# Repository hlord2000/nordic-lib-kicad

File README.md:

# Nordic Semiconductor KiCad Library

---
# A KiCad 10 library for all modern Nordic Semiconductor parts.

KLC compliance is established using KiCad's official scripts within the "kicad-library-utils" folder and the "lib_check.sh" script

Compliance for the purposes of this library is defined as zero errors for footprints and symbols. Reasonable warnings about pin position or names may be accepted.

## Installation instructions

Open the KiCad Plugin and Content Manager (PCM), click "Manage..." in the top right, and add the following URL to your list of repositories:
```
https://raw.githubusercontent.com/hlord2000/hlord2000-kicad-repository/main/repository.json
```
Then, using the dropdown in the PCM, switch to "hlord2000's KiCad Repository" and click on the "Libraries" tab.

## Seeking pull-requests for any footprint/symbol/reference design block/3D model marked 🚧

 # nRF9 series - Cellular

|             | Symbol | Footprint | Reference Design Block | 3D Model | KLC Compliant |
|-------------|--------|-----------|------------------------|----------|---------------|
| [nRF9151](https://www.nordicsemi.com/products/nrf9151) LGA |✅|✅|🚧|✅|🚧|
| [nRF9161](https://www.nordicsemi.com/products/nrf9161) LGA |✅|✅|🚧|✅|🚧|
| [nRF9160](https://www.nordicsemi.com/products/nrf9160) LGA |✅|✅|🚧|✅|🚧|

 # nRF7 series - Wi-Fi

|             | Symbol | Footprint | Reference Design Block | 3D Model | KLC Compliant |
|-------------|--------|-----------|------------------------|----------|---------------|
| [nRF7002](https://www.nordicsemi.com/products/nrf7002) QFN |✅|✅|🚧|✅|🚧| 
| [nRF7002](https://www.nordicsemi.com/products/nrf7002) WLCSP |✅|✅|🚧|✅|🚧| 
| [nRF7001](https://www.nordicsemi.com/products/nrf7001) QFN |✅|✅|🚧|✅|🚧| 
| [nRF7000](https://www.nordicsemi.com/products/nrf7000) QFN |✅|✅|🚧|✅|🚧| 

# nRF54L series - Bluetooth Low Energy

|             | Symbol | Footprint | Reference Design Block | 3D Model | KLC Compliant |
|-------------|--------|-----------|------------------------|----------|---------------|
| [nRF54LM20A](https://www.nordicsemi.com/Products/nRF54LM20A) QFN-52 |✅|✅|✅|✅|🚧| 
| [nRF54LM20A](https://www.nordicsemi.com/Products/nRF54LM20A) FCCSP |✅|✅|✅|✅|🚧| 
| [nRF54L15](https://www.nordicsemi.com/products/nrf54l15) QFN-52 |✅|✅|✅|✅|🚧| 
| [nRF54L15](https://www.nordicsemi.com/products/nrf54l15) QFN-48 |✅|✅|✅|✅|🚧| 
| [nRF54L15](https://www.nordicsemi.com/products/nrf54l15) QFN-40 |✅|✅|✅|✅|🚧| 
| [nRF54L15](https://www.nordicsemi.com/products/nrf54l15) WLCSP |✅|✅|✅|✅|🚧| 
| [nRF54L10](https://www.nordicsemi.com/products/nrf54l10) QFN-52 |✅|✅|✅|✅|🚧| 
| [nRF54L10](https://www.nordicsemi.com/products/nrf54l10) QFN-48 |✅|✅|✅|✅|🚧| 
| [nRF54L10](https://www.nordicsemi.com/products/nrf54l10) QFN-40 |✅|✅|✅|✅|🚧| 
| [nRF54LV10A](https://www.nordicsemi.com/products/nrf54lv10) CSP-29 |✅|✅|🚧|✅|🚧| 
| [nRF54LV10A](https://www.nordicsemi.com/products/nrf54lv10) QFN-48 |✅|✅|🚧|✅|🚧| 
| [nRF54LS05A](https://www.nordicsemi.com/Products/nRF54LS05A) QFN-48 |✅|✅|🚧|✅|🚧| 
| [nRF54LS05B](https://www.nordicsemi.com/Products/nRF54LS05B) QFN-48 |✅|✅|🚧|✅|🚧| 
| [nRF54L05](https://www.nordicsemi.com/products/nrf54l05) QFN-52 |✅|✅|✅|✅|🚧| 
| [nRF54L05](https://www.nordicsemi.com/products/nrf54l05) QFN-48 |✅|✅|✅|✅|🚧| 
| [nRF54L05](https://www.nordicsemi.com/products/nrf54l05) QFN-40 |✅|✅|✅|✅|🚧| 

 # nRF53 series - Bluetooth Low Energy

|             | Symbol | Footprint | Reference Design Block | 3D Model | KLC Compliant |
|-------------|--------|-----------|------------------------|----------|---------------|
| [nRF5340](https://www.nordicsemi.com/products/nrf5340) aQFN |✅|✅|🚧|🚧|🚧| 
| [nRF5340](https://www.nordicsemi.com/products/nrf5340) WLCSP |✅|✅|🚧|🚧|🚧| 

 # nRF52 series - Bluetooth Low Energy

|             | Symbol | Footprint | Reference Design Block | 3D Model | KLC Compliant |
|-------------|--------|-----------|------------------------|----------|---------------|
| [nRF52840](https://www.nordicsemi.com/products/nrf52840) aQFN |✅|✅|🚧|✅|🚧| 
| [nRF52840](https://www.nordicsemi.com/products/nrf52840) WLCSP |✅|✅|🚧|🚧|🚧| 
| [nRF52840](https://www.nordicsemi.com/products/nrf52840) QFN |✅|✅|🚧|✅|🚧| 
| [nRF52833](https://www.nordicsemi.com/products/nrf52833) aQFN |✅|✅|🚧|🚧|🚧| 
| [nRF52833](https://www.nordicsemi.com/products/nrf52833) WLCSP |✅|✅|🚧|🚧|🚧| 
| [nRF52833](https://www.nordicsemi.com/products/nrf52833) QFN |✅|✅|🚧|✅|🚧| 
| [nRF52832](https://www.nordicsemi.com/products/nrf52832) WLCSP |✅|✅|🚧|🚧|🚧| 
| [nRF52832](https://www.nordicsemi.com/products/nrf52832) QFN |✅|✅|🚧|✅|🚧| 
| [nRF52820](https://www.nordicsemi.com/products/nrf52820) WLCSP |✅|✅|🚧|🚧|🚧| 
| [nRF52820](https://www.nordicsemi.com/products/nrf52820) QFN |✅|✅|🚧|✅|🚧| 
| [nRF52811](https://www.nordicsemi.com/products/nrf52811) WLCSP |✅|✅|🚧|✅|🚧| 
| [nRF52811](https://www.nordicsemi.com/products/nrf52811) QFN-32 |✅|✅|🚧|✅|🚧| 
| [nRF52811](https://www.nordicsemi.com/products/nrf52811) QFN-48 |✅|✅|🚧|✅|🚧| 
| [nRF52810](https://www.nordicsemi.com/products/nrf52810) WLCSP |✅|✅|🚧|✅|🚧| 
| [nRF52810](https://www.nordicsemi.com/products/nrf52810) QFN-32 |✅|✅|🚧|✅|🚧| 
| [nRF52810](https://www.nordicsemi.com/products/nrf52810) QFN-48 |✅|✅|🚧|✅|🚧| 
| [nRF52805](https://www.nordicsemi.com/products/nrf52805) WLCSP |✅|✅|🚧|✅|🚧| 

 # nRF52 series - Modules

|             | Symbol | Footprint | Reference Design Block | 3D Model | KLC Compliant |
|-------------|--------|-----------|------------------------|----------|---------------|
| [E73-2G4M08S1C](https://www.ebyte.com/product-view-news.html?id=787) LGA module |✅|✅|🚧|✅|🚧|
| [ISP1907-LL](https://www.insightsip.com/products/bluetooth-low-energy/isp1907) LGA module |✅|✅|🚧|✅|🚧|

 # nRF21 series - PA + LNA ICs

|             | Symbol | Footprint | Reference Design Block | 3D Model | KLC Compliant |
|-------------|--------|-----------|------------------------|----------|---------------|
| [nRF21540](https://www.nordicsemi.com/products/nrf21540) QFN |✅|✅|🚧|✅|✅| 

 # nRF53 series - Modules

|             | Symbol | Footprint | Reference Design Block | 3D Model | KLC Compliant |
|-------------|--------|-----------|------------------------|----------|---------------|
| [E83-2G4M03S](https://www.ebyte.com/product-view-news.html?id=1307) LGA module |✅|✅|🚧|✅|🚧|
| [ISP2053-AX](https://www.insightsip.com/products/bluetooth-low-energy-and-802-15-4/isp2053) LGA module |✅|✅|🚧|✅|🚧|

 # nRF54 series - Modules

|             | Symbol | Footprint | Reference Design Block | 3D Model | KLC Compliant |
|-------------|--------|-----------|------------------------|----------|---------------|
| BC15C LGA module |✅|✅|🚧|✅|🚧|
| BC15M LGA module |✅|✅|🚧|✅|🚧|
| BL54L15-453-000xxx LGA module |✅|✅|🚧|✅|🚧|
| BL54L10-453-000xxx LGA module |✅|✅|🚧|✅|🚧|
| BM15x LGA module |✅|✅|🚧|✅|🚧|
| BM20x LGA module |✅|✅|🚧|✅|🚧|

 # nPM Power Management ICs

|             | Symbol | Footprint | Reference Design Block | 3D Model | KLC Compliant |
|-------------|--------|-----------|------------------------|----------|---------------|
| [nPM6001](https://www.nordicsemi.com/products/nPM6001) WLCSP |✅|✅|🚧|🚧|✅| 
| [nPM2100](https://www.nordicsemi.com/products/nPM2100) WLCSP |✅|✅|🚧|✅|✅| 
| [nPM2100](https://www.nordicsemi.com/products/nPM2100) QFN |✅|✅|🚧|✅|✅| 
| [nPM1300](https://www.nordicsemi.com/products/nPM1300) WLCSP |✅|✅|🚧|🚧|✅| 
| [nPM1300](https://www.nordicsemi.com/products/nPM1300) QFN |✅|✅|🚧|✅|✅| 
| [nPM1100](https://www.nordicsemi.com/products/nPM1100) WLCSP |✅|✅|🚧|🚧|✅| 
| [nPM1100](https://www.nordicsemi.com/products/nPM1100) QFN |✅|✅|🚧|✅|✅|

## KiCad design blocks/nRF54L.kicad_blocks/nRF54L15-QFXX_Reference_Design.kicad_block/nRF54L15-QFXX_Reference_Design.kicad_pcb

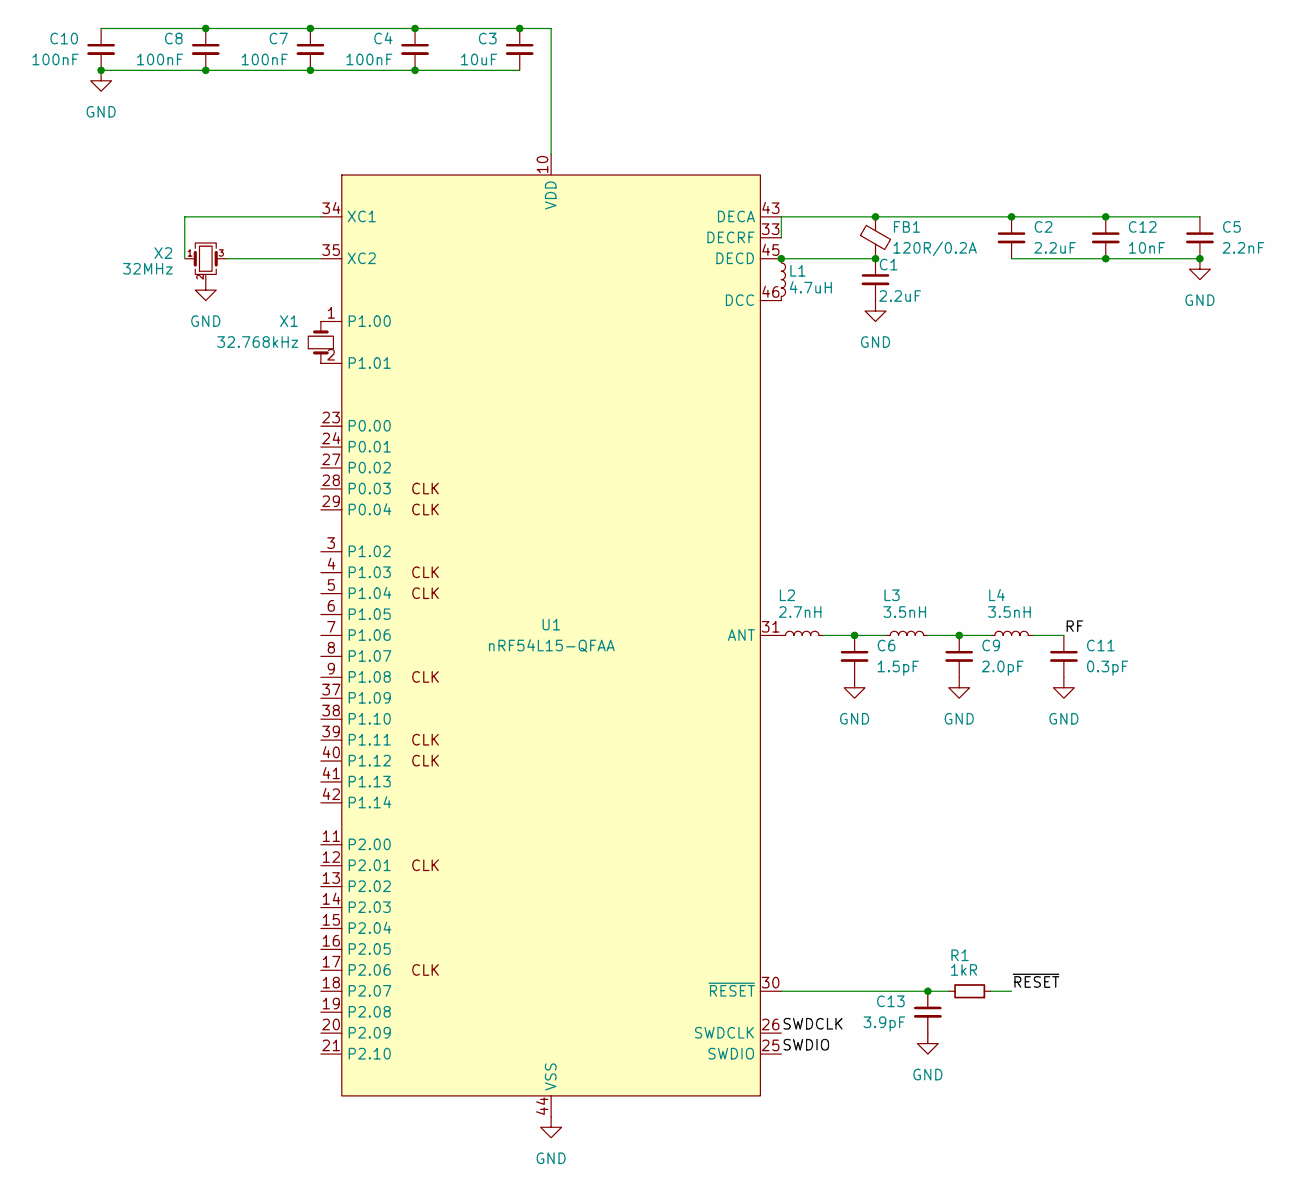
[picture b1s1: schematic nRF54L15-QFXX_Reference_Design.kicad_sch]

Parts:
C1, C2: 2.2uF; C_0201_0603Metric_L
C3: 10uF; C_0402_1005Metric_L
C4, C7, C8, C10: 100nF; C_0201_0603Metric_L
C5: 2.2nF; C_0201_0603Metric_L
C6: 1.5pF; C_0201_0603Metric_L
C9: 2.0pF; C_0201_0603Metric_L
C11: 0.3pF; C_0201_0603Metric_L
C12: 10nF; C_0201_0603Metric_L
C13: 3.9pF; C_0201_0603Metric_L
FB1: 120R/0.2A; L_0201_0603Metric_L
L1: 4.7uH; L_0603_1608Metric_L
L2: 2.7nH; L_0201_0603Metric_L
L3, L4: 3.5nH; L_0201_0603Metric_L
R1: 1kR; R_0201_0603Metric_L
U1: nRF54L15-QFAA; QFN-48-1EP_6x6mm_P0.4mm_EP4.6x4.6mm_ThermalVias
X1: 32.768kHz; Crystal_SMD_2012-2Pin_2.0x1.2mm
X2: 32MHz; Crystal_SMD_2016-4Pin_2.0x1.6mm

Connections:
/RF: C11.1, L4.2
/SWDCLK: U1.26 (SWDCLK)
/SWDIO: U1.25 (SWDIO)
/~RESET: R1.1
GND: C1.2, C2.2, C3.2, C4.2, C5.2, C6.2, C7.2, C8.2, C9.2, C10.2, C11.2, C12.2, C13.2, U1.32 (VSS_PA), U1.44 (VSS), U1.49 (VSS), X2.2 (G), X2.4 (G)
unnamed: C6.1, L2.2, L3.1
unnamed: C9.1, L3.2, L4.1
unnamed: C3.1, C4.1, C7.1, C8.1, C10.1, U1.10 (VDD), U1.22 (VDD), U1.36 (VDD), U1.47 (VDD), U1.48 (VDD)
unnamed: L2.1, U1.31 (ANT)
unnamed: L1.2, U1.46 (DCC)
unnamed: C2.1, C5.1, C12.1, FB1.1, U1.33 (DECRF), U1.43 (DECA)
unnamed: C1.1, FB1.2, L1.1, U1.45 (DECD)
unnamed: U1.1 (P1.00), X1.2
unnamed: U1.2 (P1.01), X1.1
unnamed: U1.34 (XC1), X2.1
unnamed: U1.35 (XC2), X2.3
unnamed: C13.1, R1.2, U1.30 (~RESET)

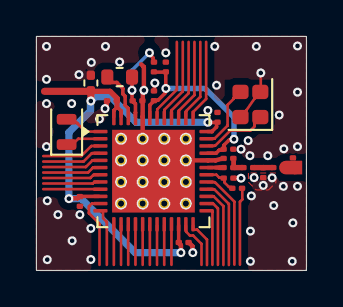
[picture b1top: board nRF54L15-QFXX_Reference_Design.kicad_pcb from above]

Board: 4 copper layers, 15.0 x 13.0 mm, 22 parts (0 on the bottom side), 14 nets.

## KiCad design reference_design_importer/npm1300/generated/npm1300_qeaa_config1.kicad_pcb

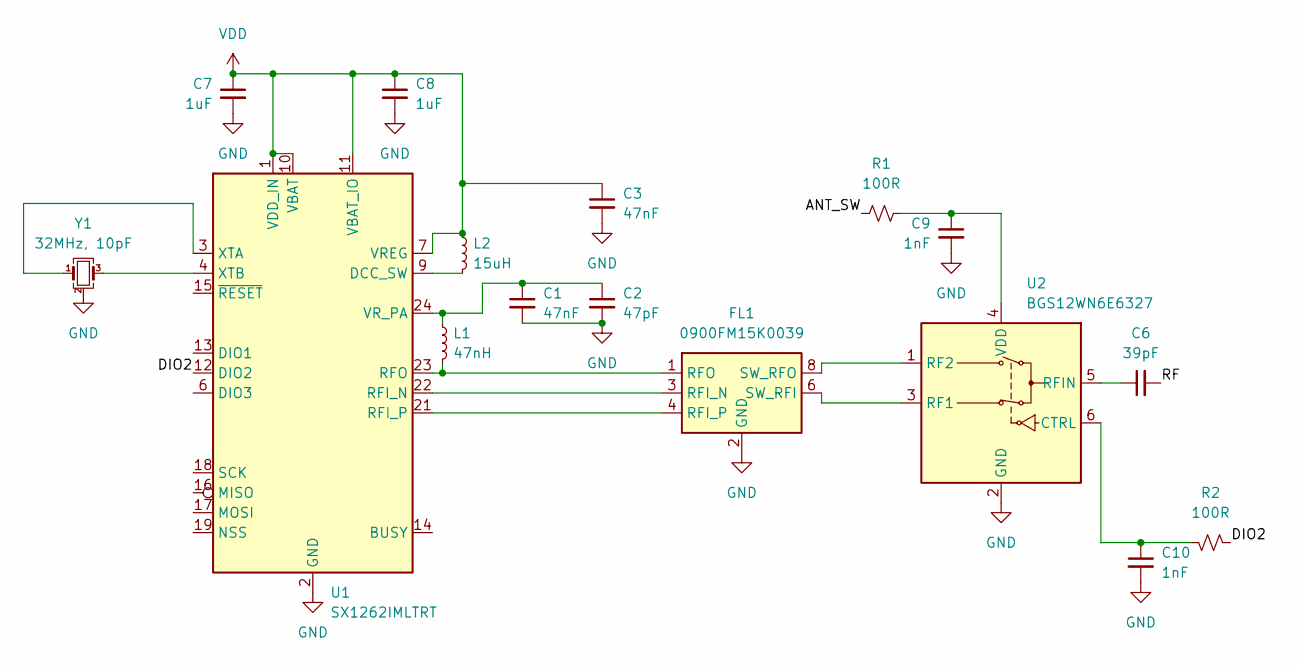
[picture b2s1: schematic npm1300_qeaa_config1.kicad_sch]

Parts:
C1, C3: 47nF; C_0201_0603Metric_L
C2: 47pF; C_0201_0603Metric_L
C6: 39pF; C_0201_0603Metric_L
C7, C8: 1uF; C_0201_0603Metric_L
C9, C10: 1nF; C_0201_0603Metric_L
FL1: 0900FM15K0039; Balun_Johanson_0900FM15K0039
L1: 47nH; L_0201_0603Metric_L
L2: 15uH; L_0603_1608Metric_L
R1, R2: 100R; C_0201_0603Metric_L
U1: SX1262IMLTRT; QFN-24-1EP_4x4mm_P0.5mm_EP2.6x2.6mm_ThermalVias
U2: BGS12WN6E6327; Infineon_PG-TSNP-6-10_0.7x1.1mm_0.7x1.1mm_P0.4mm
Y1: 32MHz, 10pF; Crystal_SMD_2016-4Pin_2.0x1.6mm

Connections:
/ANT_SW: R1.1
/DIO2: R2.1, U1.12 (DIO2)
/RF: C6.2
GND: C1.2, C2.2, C3.2, C7.2, C8.2, C9.2, C10.2, FL1.2 (GND), FL1.5 (GND), FL1.7 (GND), FL1.9 (GND), FL1.10 (GND), U1.2 (GND), U1.5 (GND), U1.8 (GND), U1.20 (GND), U1.25 (GND), U2.2 (GND), Y1.2 (G), Y1.4 (G)
unnamed: FL1.3 (RFI_N), U1.22 (RFI_N)
unnamed: FL1.4 (RFI_P), U1.21 (RFI_P)
unnamed: FL1.1 (RFO), L1.2, U1.23 (RFO)
unnamed: FL1.6 (SW_RFI), U2.3 (RF1)
unnamed: FL1.8 (SW_RFO), U2.1 (RF2)
unnamed: L2.2, U1.9 (DCC_SW)
unnamed: C3.1, C7.1, C8.1, L2.1, U1.1 (VDD_IN), U1.7 (VREG), U1.10 (VBAT), U1.11 (VBAT_IO)
unnamed: C1.1, C2.1, L1.1, U1.24 (VR_PA)
unnamed: U1.3 (XTA), Y1.1
unnamed: U1.4 (XTB), Y1.3
unnamed: C10.1, R2.2, U2.6 (CTRL)
unnamed: C6.1, U2.5 (RFIN)
unnamed: C9.1, R1.2, U2.4 (VDD)

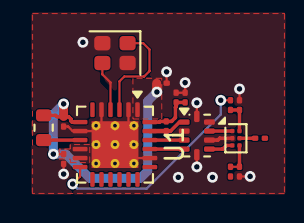
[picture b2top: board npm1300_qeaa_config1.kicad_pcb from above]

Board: 4 copper layers, 16 parts (0 on the bottom side), 15 nets.

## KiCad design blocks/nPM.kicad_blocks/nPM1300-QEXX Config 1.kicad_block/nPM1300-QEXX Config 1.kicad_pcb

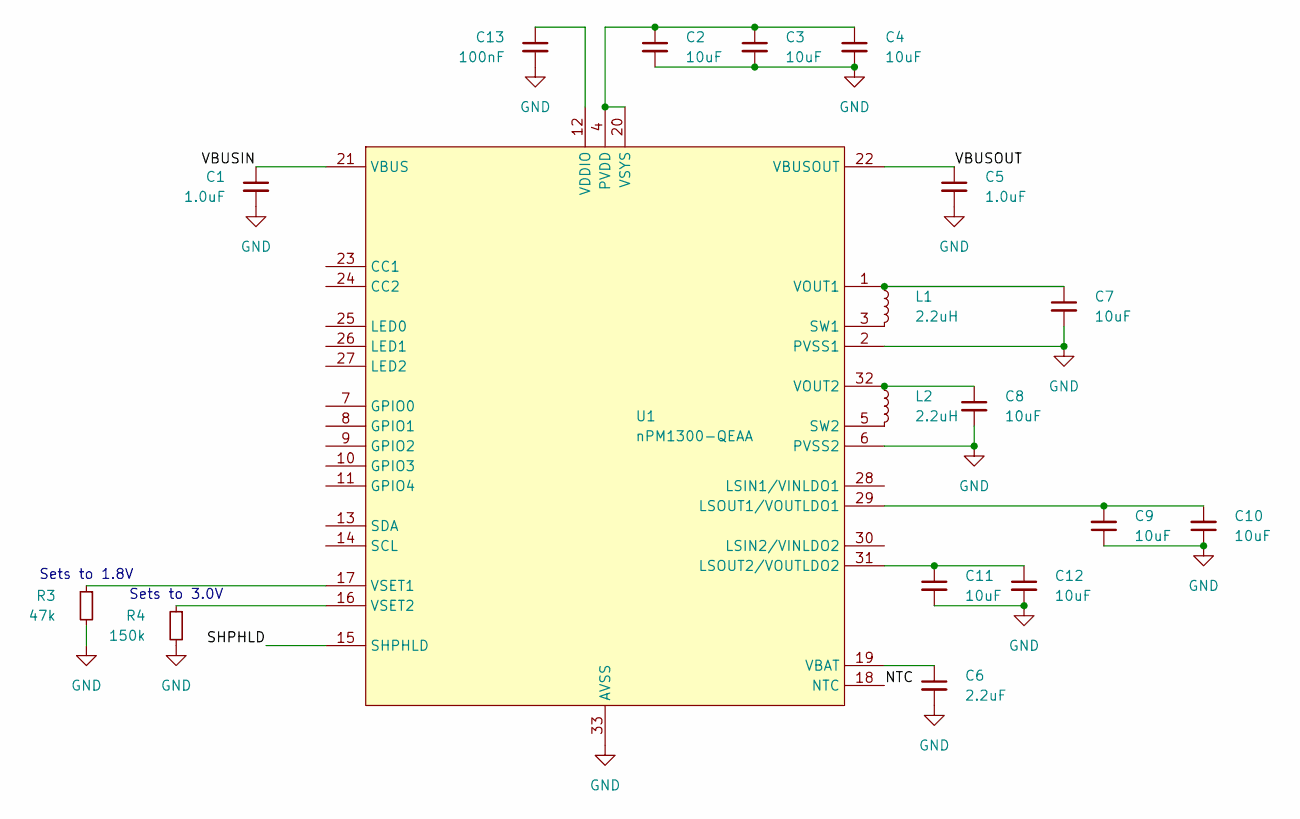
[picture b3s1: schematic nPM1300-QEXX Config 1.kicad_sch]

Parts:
C1, C5: 1.0uF; C_0603_1608Metric_L
C2, C3, C4, C7, C8, C9, C10, C11, C12: 10uF; C_0603_1608Metric_L
C6: 2.2uF; C_0603_1608Metric_L
C13: 100nF; C_0201_0603Metric_L
L1, L2: 2.2uH; L_0806_2016Metric_L
R3: 47k; R_0201_0603Metric_L
R4: 150k; R_0201_0603Metric_L
U1: nPM1300-QEAA; QFN-32-1EP_5x5mm_P0.5mm_EP3.6x3.6mm_ThermalVias

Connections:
/NTC: U1.18 (NTC)
/SHPHLD: U1.15 (SHPHLD)
/VBUSIN: C1.1, U1.21 (VBUS)
/VBUSOUT: C5.1, U1.22 (VBUSOUT)
GND: C1.2, C2.2, C3.2, C4.2, C5.2, C6.2, C7.2, C8.2, C9.1, C10.1, C11.2, C12.2, C13.2, R3.2, R4.2, U1.2 (PVSS1), U1.6 (PVSS2), U1.33 (AVSS)
unnamed: C9.2, C10.2, U1.29 (LSOUT1/VOUTLDO1)
unnamed: C11.1, C12.1, U1.31 (LSOUT2/VOUTLDO2)
unnamed: C2.1, C3.1, C4.1, U1.4 (PVDD), U1.20 (VSYS)
unnamed: L1.2, U1.3 (SW1)
unnamed: L2.1, U1.5 (SW2)
unnamed: C6.1, U1.19 (VBAT)
unnamed: C13.1, U1.12 (VDDIO)
unnamed: C7.1, L1.1, U1.1 (VOUT1)
unnamed: C8.1, L2.2, U1.32 (VOUT2)
unnamed: R3.1, U1.17 (VSET1)
unnamed: R4.1, U1.16 (VSET2)

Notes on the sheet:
Sets to 1.8V
Sets to 3.0V

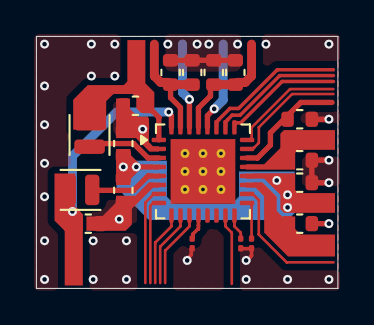
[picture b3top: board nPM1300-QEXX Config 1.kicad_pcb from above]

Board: 4 copper layers, 16.8 x 14.0 mm, 18 parts (0 on the bottom side), 14 nets.

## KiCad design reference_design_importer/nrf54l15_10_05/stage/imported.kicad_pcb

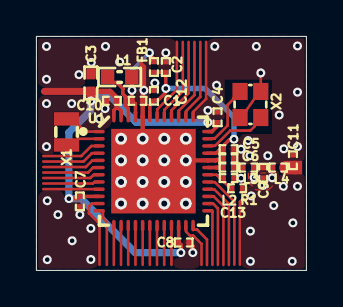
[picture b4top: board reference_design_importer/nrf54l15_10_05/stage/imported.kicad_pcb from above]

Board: 4 copper layers, 15.0 x 13.0 mm, 22 parts (0 on the bottom side), 14 nets.

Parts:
C1, C2: 2.2µF; CAPC0603X03L_C
C3: 10µF; CAPC1005X04L
C4, C7, C8, C10: 100nF; CAPC0603X03L_C
C5: 2.2nF; CAPC0603X03L_C
C6: 1.5pF; CAPC0603X03L_C
C9: 2.0pF; CAPC0603X03L_C
C11: 0.3pF; CAPC0603X03L_C
C12: 10nF; CAPC0603X03L_C
C13: 3.9pF; CAPC0603X03L_C
FB1: 120R/0.2A; INDC0603X03L_C
L1: 4.7µH; INDC1608X06L
L2: 2.7nH; INDC0603X03L_C
L3, L4: 3.5nH; INDC0603X03L_C
R1: 1k; RESC0603X03L_C
U1: nRF54L15-QFAA; QFN40P600X600X90-48N
X1: 32.768kHz; XTAL_2012
X2: 32MHz; BT-XTAL_2016

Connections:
DCC: L1.1, U1.46
DECA: C2.2, C5.2, C12.2, FB1.2, U1.33, U1.43
DECD: C1.2, FB1.1, L1.2, U1.45
GND: C1.1, C2.1, C3.1, C4.2, C5.1, C6.1, C7.2, C8.2, C9.1, C10.2, C11.1, C12.1, C13.1, U1.32, U1.44, U1.49, X2.2, X2.4
NetC6_2: C6.2, L2.2, L3.1
NetC9_2: C9.2, L3.2, L4.1
NetC13_2: C13.2, R1.1, U1.30
NetL2_1: L2.1, U1.31
P1.00/XL1: U1.1, X1.2
P1.01/XL2: U1.2, X1.1
RF: C11.2, L4.2
VDD_NRF: C3.2, C4.1, C7.1, C8.1, C10.1, U1.10, U1.22, U1.36, U1.47, U1.48
XC1: U1.34, X2.1
XC2: U1.35, X2.3

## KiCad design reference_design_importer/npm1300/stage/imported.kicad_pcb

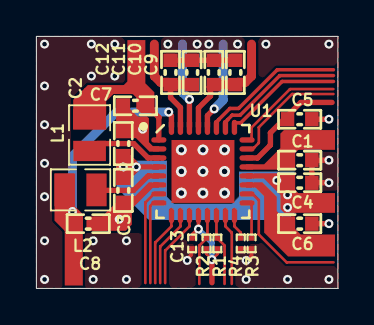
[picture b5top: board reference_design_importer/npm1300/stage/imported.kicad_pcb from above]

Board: 4 copper layers, 16.8 x 14.0 mm, 22 parts (0 on the bottom side), 18 nets.

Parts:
C1, C5: 1.0µF; CAPC1608X06L
C2, C3, C4, C7, C8, C9, C10, C11, C12: 10µF; CAPC1608X06L
C6: 2.2µF; CAPC1608X06L
C13: 100nF; CAPC0603X03L_C
L1, L2: 2.2µH; INDC2016X10N
NT1, NT2: Net tie; 2 PIN STARPOINT
R1, R2: 10k; RESC0603X03L_C
R3: 47k; RESC0603X03L_C
R4: 150k; RESC0603X03L_C
U1: nPM1300-QEAA; Nordic_QFN50P500X500X90-33N

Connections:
GND: C1.1, C4.1, C5.1, C6.1, C9.1, C10.1, C11.1, C12.1, C13.2, NT1.1, NT2.1, R3.2, R4.2, U1.33
PVSS1: C2.1, C7.1, NT1.2, U1.2
PVSS2: C3.1, C8.1, NT2.2, U1.6
SCL: R1.1, U1.14
SDA: R2.1, U1.13
SW1: L1.2, U1.3
SW2: L2.2, U1.5
VBAT: C6.2, U1.19
VBUSIN: C1.2, U1.21
VBUSOUT: C5.2, U1.22
VDDIO: C13.1, R1.2, R2.2, U1.12
VOUT1: C7.2, L1.1, U1.1
VOUT2: C8.2, L2.1, U1.32
VOUTLDO1: C9.2, C10.2, U1.29
VOUTLDO2: C11.2, C12.2, U1.31
VSET1: R3.1, U1.17
VSET2: R4.1, U1.16
VSYS: C2.2, C3.2, C4.2, U1.4, U1.20

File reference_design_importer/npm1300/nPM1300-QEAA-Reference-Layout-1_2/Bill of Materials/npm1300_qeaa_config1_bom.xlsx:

| Bill of Materials
 | Device: | nPM1300-QEAA
 | Configuration No.: | 1
 | Reference Layout Title: | Full – both BUCKs and LDOs, VINLDO from external sources
 | Revision: | 1.2
 | Creation Date: | 2025-06-05
 | Designator | Value | Description | Footprint Doc | Manufacturer | Manufacturer Part Number | #Column Name Error:' Fitted | Quantity
 | C1, C5 | 1.0µF | Capacitor, Ceramic, 1.0µF 10V X5R 0603,±10% | 0603 | N.A. | N.A. |  | 2
 | C2, C3, C4, C7, C8, C9, C10, C11, C12 | 10µF | Capacitor, X5R, ±20% | 0603 | N.A. | N.A. |  | 9
 | C6 | 2.2µF | Capacitor, Ceramic, X7R, ±10%, 16V | 0603 | Taiyo Yuden | EMK107BB7225KA-T |  | 1
 | C13 | 100nF | Capacitor, X5R, ±10%, 100nF, 16V | 0201 | N.A. | N.A. |  | 1
 | L1, L2 | 2.2µH | Inductor, Irms=2.5A, Isat=2.9A, ±20%, DCR=73mΩ | 0806 | Samsung Electro-Mechanics America | CIGT201610EH2R2MNE |  | 2
 | R1, R2 | 10k | Resistor, ±1%, 0.05W | 0201 | N.A. | N.A. |  | 2
 | R3 | 47k | Resistor, ±1%, 0.05W | 0201 | N.A. | N.A. |  | 1
 | R4 | 150k | Resistor, ±1%, 0.05W | 0201 | N.A. | N.A. |  | 1
 | U1 | nPM1300-QEAA | Li-Ion/Li-Polymer USB-C battery charger with high efficiency buck regulators, L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 | QFN-32 | Nordic Semiconductor | nPM1300-QEAA |  | 1
 |  |  |  |  |  |  |  | 20

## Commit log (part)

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2023-06-09 Initial commit.
2023-06-09 Added readme
2023-06-09 Added nRF21540 FEM
2023-06-09 Added footprints for nPM1100, nRF21540, nRF7002, nRF5340 WLCSP.
2023-06-13 Modified nRF53 symbol
2023-06-16 Adjusted nRF700x
2023-06-28 Added nPM1300
2023-07-21 Added libmanagement and continued creating symbols.
2023-07-21 Cleaned libmanagement
2023-07-21 removed fp-info-cache
2023-07-21 Symbols for nPM6001 and nPM1300 in CSP
2023-07-21 Added symbols for nRF52820, adjusted groupings for nRF9160
2023-07-21 Added symbols for nRF52832 and nRF52833.
2023-07-21 nRF52833-QDXX
2023-07-22 Added final nRF52 symbols
2023-07-22 Added nrf9160 symbol
2023-07-22 Added footprints that exist in KiCAD already.
2023-07-22 Added support table.
2023-07-22 Adjusted support table.
2023-07-22 adjusted table headings
2023-07-22 Combined nRF52840 tables
2023-07-22 Added product links.
2023-07-22 added license
2023-07-22 Added workflow
2023-07-22 Fixed download URL
2023-07-22 ADded resources.zip
2023-07-22 Adjusted resources.zip
2023-07-22 Updated resources.
2023-07-24 Removed resources folder.
2023-07-24 Fixed supported list. Added request for PRs
2023-07-24 Fixed duplication of efforts w.r.t. QFN footprints already in KiCAD 7. Finalized aQFN for 5340. Added 7001 footprint and symbol. Updated README to reflect changes.
2023-07-24 Added pull request template.
2023-07-24 Added reference to 3D models needed
2023-07-24 Added WLCSP footprint for nRF52840
2023-07-24 Added WLCSP footprint for nPM1300
2023-07-24 Added LGA footprint for nRF9160
2023-07-24 Added WLCSP footprint for nPM6001
2023-07-24 Added nRF52832 WLCSP footprint
2023-07-24 Added nRF52833 WLCSP footprint
2023-07-24 Added nRF52811/nRF52810 WLCSP footprint and nRF52820 WLCSP footprint
2023-07-24 Added aQFN footprint reference for nRF52833
2023-07-24 Fixed broken footprints
2023-07-27 Update LICENSE
    Changed license
2023-07-31 Added some 3d models and fixed directory for 3d models.
2023-07-31 Update README.md with new 3D files
2023-09-07 Added reference to nRF7000
2023-09-23 Modified nPM1100/nPM1300 to get closer to KLC compliance. Added lib_check to check all symbols and footprints.
2023-09-23 Adjusted README
2023-09-25 Fixes for nPM1300 and nPM6001
2023-10-07 modified pin length for nrf53
2023-10-27 nRF52840-QFXX: fixed overlapping pins.
2023-11-14 nRF7000: Symbol Definition
    Added symbol definition for nRF7000, using KiCAD Library QFN footprint.
2023-11-14 Updated readme for nRF7000
2023-11-14 Added README image
2023-12-09 symbols: revert to stable version (7.0)
    Reverted symbols in nRF5 and nRF7 libraries to use
    stable KiCAD versions.
    Per: https://github.com/hlord2000/nordic-lib-kicad/issues/2
2023-12-09 symbols: fixed footprint assocations
    When the library is run through PCM actions,
    it has "PCM_" appended to the library name for
    footprints. This just adds "PCM_" to the beginning
    of all symbol assigned footprints.
    Fixes issue #3
2023-12-09 symbols: nrf21540 KLC compliance
    Modified nRF21540 for KLC compliance.
2023-12-09 readme: updated nPM KLC
    KLC fails for nPM but errors are considered to be acceptable
2023-12-09 ci: updated workflow script for changes only
    CI now only checks changed files in PR
2023-12-28 Added E73-2G4M08S1C nRF52840 Module
2024-01-19 Added nRF9161 and fixed nRF9160 footprint
2024-02-28 Add files via upload
    Added 3D step files for nrF5340 aQFN94 7 x 7mm SoC and nrf5340 WLSP 4.4 x 4.0mm SoC
2024-02-28 Added nrF9161 and nrF9160 SiP 3D models
    Added nrF9161 SiP 3D Model and nrF9160 3D Model extracted from DK hardware and Thingy 91 hardware files
2024-03-06 Added 52833 & 52840 3D models
    Adding in 52833 WLCSP and 52833 aQFN 3D models as well as the 52840 WLCSP 3D model as well. Models from Nordic Example Design Guide Hardware files or DKs
2024-03-09 folder for Nordic nPM 3D models
    Uploading Nordic nPM 3D models for merge with upstream repo
2024-03-09 Adding 3D models for nPM modules
    added in WLCSP models for the nPM1100, nPM1300 and nPM6001 Modules
2024-03-10 3dmodels: nrf9
    Added step files w/ redefined origin and renamed from:
    37b1c0c5198b7eb3ca5ebfcd8d5ff384124a1ade
2024-03-10 lib: updated to KiCAD 8
    update paths for 3dmodels and readme to reference
    KiCAD 8
2024-03-10 lib: modified PCM version
    Fixed PCM script to allow KiCAD 8 release.
2024-03-10 footprints: fix nrf9161 alignment
    restore footprint model alignment to 0,0,0
2024-03-10 readme: nrf916x updated status
    updated status of nrf916x to reflect
    added 3d models
2024-03-31 Correct npm1100 footprint errors (fixes #11)
2024-03-31 align pins to 100mil grid
2024-04-19 symbols: nrf91: added pin definitions
    Added pin definitions for nRF916X parts.
    Closes issue #13
2024-05-07 Add npm1100 QFN24 center pad (pin 25) as AVSS
    According to
    [this devzone answer](https://devzone.nordicsemi.com/f/nordic-q-a/110896/help-with-strange-npm1100-performance),
    the center pad should be connected to AVSS (ground). This is not
    documented directly in the product specification, only hinted at by the
    example schematics.
2024-05-07 Overlap pin 25 (EP) with corresponding AVSS pin and make it invisible
2024-05-23 nrf52: modules: add isp1907
    Add footprint and symbol for the ISP1907-LL,
    nRF52811 SiP from ISP.
2024-05-23 Updated gitignore
2024-05-23 symbols: isp2053: fix NC pins
    Moved NC pins for compliance with KLC
2024-05-23 modules: isp: updated footprints
    Updated footprints for ISP LGAs fixing
    issue w/ new ISP1907 having spurious dimension in silkscreen
2024-06-03 device: nrf9151
    Add nRF9151 symbol and footprint
2024-06-03 footprints: nrf9160
    Small change to description of nrf9160 footprint
2024-06-03 readme: nrf9151
    Adds reference to nRF9151 in readme
2024-07-10 Symbol updates, pin length, pin type
2024-07-13 nrf53: update 5340
    Updated nRF5340 symbol w/ datasheet link and
    KiCAD included aQFN footprint
2024-07-20 3dmodels: added E73-2G4M08S1C nRF52840 module
2024-08-01 footprints: nrf91x: solder paste expansion
    Modified solder paste expansion values for improved
    solder performance, per internal ticket.
2024-08-14 devices: nrf7002: added CSP
    Adds CSP variant of nRF7002
2024-09-03 nrf53: modules: add E83-2G4M03S
    Adds the E83-2G4M03S module, available for assembly
    at JLCPCB
2024-09-30 symbols: npm1300: moved power pins
    Move power pins for easier routing
2024-10-10 device: nrf54: added fanstel modules
    Added fanstel modules for nRF54 series
2024-10-21 Update 9151 3D Model
2024-10-31 Added nRF9151 3D model
2024-10-31 Added automatic addition of PCM_ prefix when library release is tagged
2024-10-31 Fixed Icon
2024-11-12 devices: add nRF54L series
    Adds nRF54L15, L10, and L05
2024-11-12 Added nRF54L15 WLCSP 3D model
2024-11-15 Updated PCM for better footprint name handling
2024-11-15 Updated nRF54L symbol w/ better layout for DC/DC
2024-12-10 design_blocks: add nRF54L reference design blocks
    Adds nRF54L series design blocks, a KiCAD 9 pre-release feature
2025-02-06 symbols: nrf52: reworked all for KLC compliance, pin types
2025-02-06 symbols: updated for KLC compliance
2025-02-06 symbols: nrf54-modules: Updated BM15x, added BC15
2025-02-24 footprints: npm1300: added csp step file
2025-03-24 Moved design blocks, changed create_pcm_archive to accomodate design blocks
2025-03-31 add npm2100
2025-03-31 Added nRF7002-CSP 3d model
2025-04-24 updated swd pinout positions
2025-04-24 add Ezurio BL54L modules
2025-09-18 Add nRF54 in QFN-40, QFN-52.
    Add nRF54 in QFN-40, QFN-52.
    Added nRF54LM20A
2025-09-18 Added nRF54LM20A and reference design
2025-09-18 Added nRF54LM20A to readme
2025-10-24 Updated nRF9151 footprint to match reference design
2025-11-24 Removed trailing comma on PCM metadata template
    Removed trailing comma after GitHub username to fix import failed on KiCad PCM import.
2025-12-03 Added nRF54LV10A
2025-12-03 Added scripts for LLM assistance in creating symbol
2025-12-03 Added LLM assistance for generating symbols from table
2025-12-03 Update sym-lib-table
2025-12-03 Updates to fix footprint mapping
2025-12-05 Added nPM1100 3D STEP Model
2025-12-05 Add nPM1100 footprint link
2025-12-05 nPM1100 3D Model: Add 0.025mm to height as nominal height was off
2026-04-05 Added nRF54LM20A-CAAA symbol and CSP-61 footprint
2026-04-14 Generate Nordic footprints from spec
2026-04-14 Updates to move to auto-generated footprints
2026-04-14 Update README status matrix
2026-04-14 Updates for nRF54LS05A/B
2026-04-14 Updates to 3d models + dirs
2026-04-21 Assign 32MHz crystal footprint and LCSC part
2026-05-06 Add AGENTS.md
2026-06-07 updates for ref design test
